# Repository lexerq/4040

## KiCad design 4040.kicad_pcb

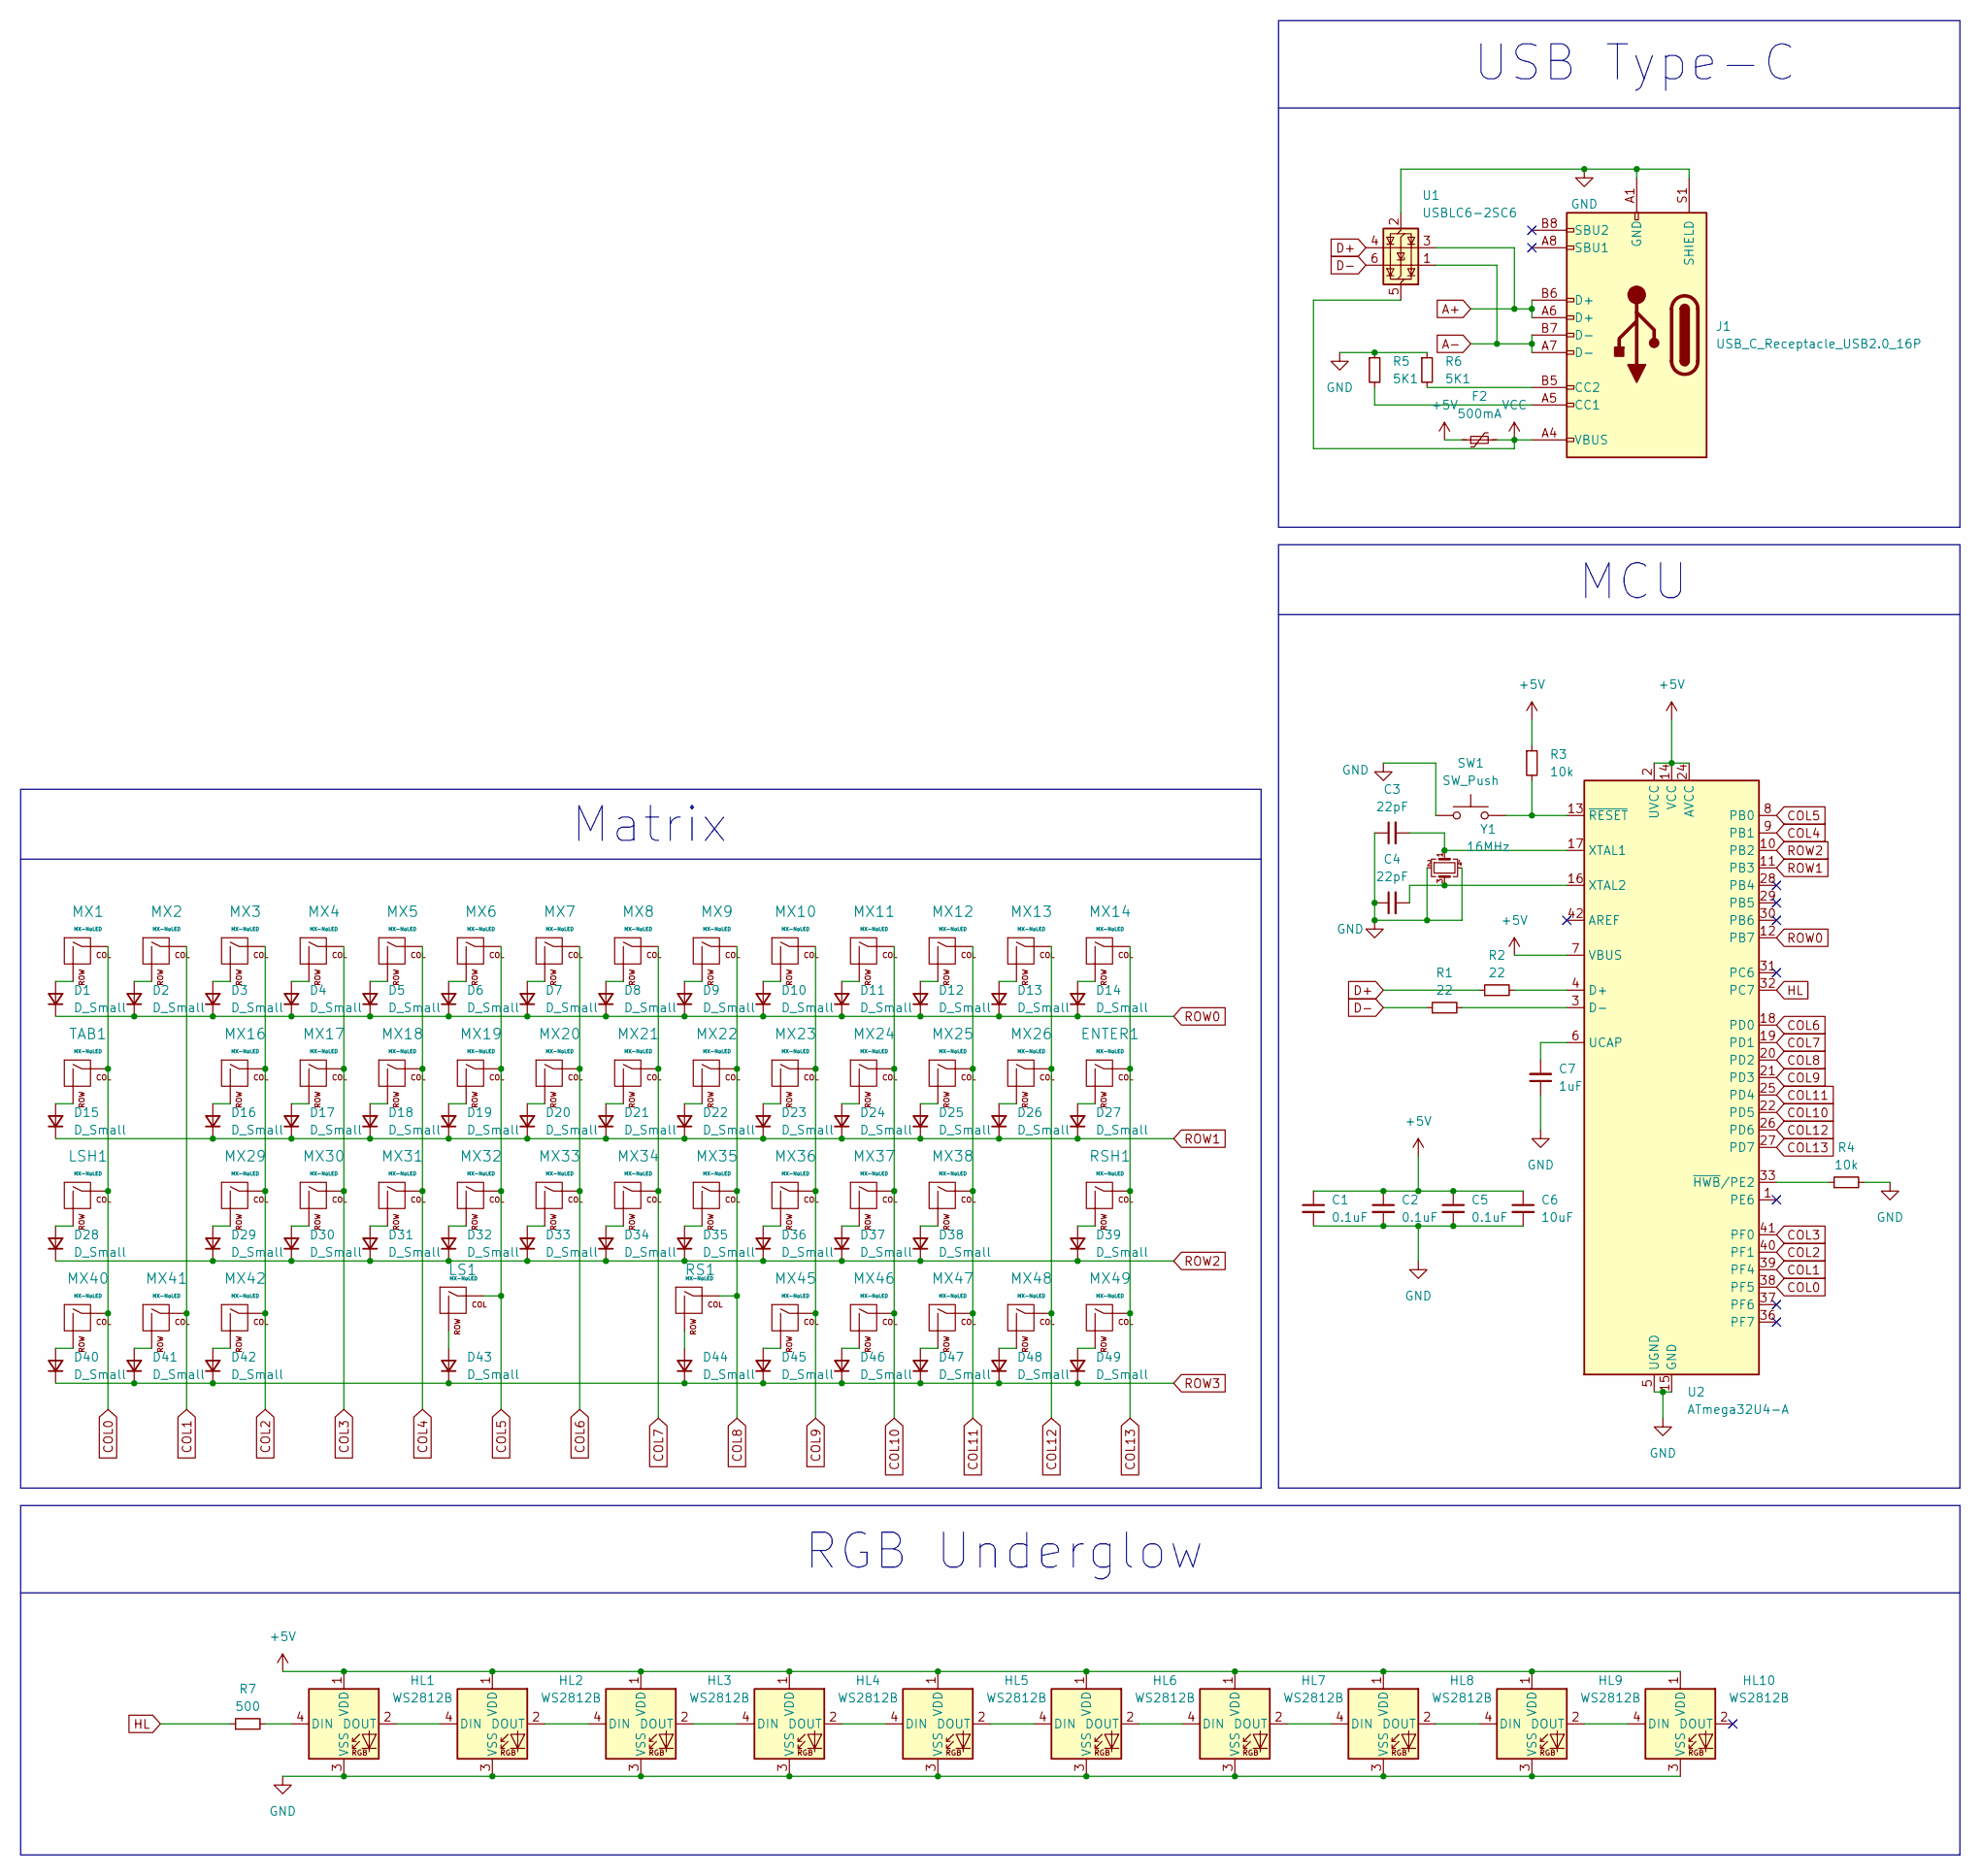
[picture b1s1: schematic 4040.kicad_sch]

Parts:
C1, C2, C5: 0.1uF; C_0805_2012Metric
C3, C4: 22pF; C_0805_2012Metric
C6: 10uF; C_0805_2012Metric
C7: 1uF; C_0805_2012Metric
D1, D2, D3, D4, D5, D6, D7, D8, D9, D10, D11, D12, D13, D14, D15, D16, D17, D18, D19, D20, D21, D22, D23, D24, D25, D26, D27, D28, D29, D30, D31, D32, D33, D34, D35, D36, D37, D38, D39, D40, D41, D42, D43, D44, D45, D46, D47, D48, D49: D_Small; 5,5ForKBD
ENTER1: MX-NoLED; MX-2.25U-NoLED
F2: 500mA; Fuse_1206_3216Metric
HL1, HL2, HL3, HL4, HL5, HL6, HL7, HL8, HL9, HL10: WS2812B; LED_WS2812B_PLCC4_5.0x5.0mm_P3.2mm
J1: USB_C_Receptacle_USB2.0_16P; USB_C_Receptacle_HRO_TYPE-C-31-M-12
LS1: MX-NoLED; MX-2.25U-ReversedStabilizers-NoLED
LSH1: MX-NoLED; MX-2U-NoLED
MX1, MX2, MX3, MX4, MX5, MX6, MX7, MX8, MX9, MX10, MX11, MX12, MX13, MX16, MX17, MX18, MX19, MX20, MX21, MX22, MX23, MX24, MX25, MX26, MX29, MX30, MX31, MX32, MX33, MX34, MX35, MX36, MX37, MX38, MX45: MX-NoLED; MX-1U-NoLED
MX14: MX-NoLED; MX-1.75U-NoLED
MX40, MX41, MX42, MX46, MX47, MX48, MX49: MX-NoLED; MX-1.25U-NoLED
R1, R2: 22; R_0805_2012Metric
R3, R4: 10k; R_0805_2012Metric
R5, R6: 5K1; R_0805_2012Metric
R7: 500; R_0805_2012Metric
RS1: MX-NoLED; MX-2.75U-ReversedStabilizers-NoLED
RSH1: MX-NoLED; MX-2.75U-NoLED
SW1: SW_Push; SW_DIP_SPSTx01_Slide_Omron_A6S-110x_W8.9mm_P2.54mm
TAB1: MX-NoLED; MX-1.5U-NoLED
U1: USBLC6-2SC6; SOT-23-6
U2: ATmega32U4-A; TQFP-44_10x10mm_P0.8mm
Y1: 16MHz; Crystal_SMD_3225-4Pin_3.2x2.5mm

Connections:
+5V: C1.1, C2.1, C5.1, C6.1, F2.1, HL1.1 (VDD), HL2.1 (VDD), HL3.1 (VDD), HL4.1 (VDD), HL5.1 (VDD), HL6.1 (VDD), HL7.1 (VDD), HL8.1 (VDD), HL9.1 (VDD), HL10.1 (VDD), R3.1, U2.2 (UVCC), U2.7 (VBUS), U2.14 (VCC), U2.24 (AVCC), U2.34 (VCC), U2.44 (AVCC)
A+: J1.A6 (D+), J1.B6 (D+), U1.3 (I/O2)
A-: J1.A7 (D-), J1.B7 (D-), U1.1 (I/O1)
COL0: LSH1.1 (COL), MX1.1 (COL), MX40.1 (COL), TAB1.1 (COL), U2.38 (PF5)
COL1: MX2.1 (COL), MX41.1 (COL), U2.39 (PF4)
COL2: MX3.1 (COL), MX16.1 (COL), MX29.1 (COL), MX42.1 (COL), U2.40 (PF1)
COL3: MX4.1 (COL), MX17.1 (COL), MX30.1 (COL), U2.41 (PF0)
COL4: MX5.1 (COL), MX18.1 (COL), MX31.1 (COL), U2.9 (PB1)
COL5: LS1.1 (COL), MX6.1 (COL), MX19.1 (COL), MX32.1 (COL), U2.8 (PB0)
COL6: MX7.1 (COL), MX20.1 (COL), MX33.1 (COL), U2.18 (PD0)
COL7: MX8.1 (COL), MX21.1 (COL), MX34.1 (COL), U2.19 (PD1)
COL8: MX9.1 (COL), MX22.1 (COL), MX35.1 (COL), RS1.1 (COL), U2.20 (PD2)
COL9: MX10.1 (COL), MX23.1 (COL), MX36.1 (COL), MX45.1 (COL), U2.21 (PD3)
COL10: MX11.1 (COL), MX24.1 (COL), MX37.1 (COL), MX46.1 (COL), U2.22 (PD5)
COL11: MX12.1 (COL), MX25.1 (COL), MX38.1 (COL), MX47.1 (COL), U2.25 (PD4)
COL12: MX13.1 (COL), MX26.1 (COL), MX48.1 (COL), U2.26 (PD6)
COL13: ENTER1.1 (COL), MX14.1 (COL), MX49.1 (COL), RSH1.1 (COL), U2.27 (PD7)
D+: R2.1, U1.4 (I/O2)
D-: R1.1, U1.6 (I/O1)
GND: C1.2, C2.2, C3.1, C4.1, C5.2, C6.2, C7.1, HL1.3 (VSS), HL2.3 (VSS), HL3.3 (VSS), HL4.3 (VSS), HL5.3 (VSS), HL6.3 (VSS), HL7.3 (VSS), HL8.3 (VSS), HL9.3 (VSS), HL10.3 (VSS), J1.A1 (GND), J1.A12 (GND), J1.B1 (GND), J1.B12 (GND), J1.S1 (SHIELD), R4.2, R5.1, R6.1, SW1.1, U1.2 (GND), U2.5 (UGND), U2.15 (GND), U2.23 (GND), U2.35 (GND), U2.43 (GND), Y1.2, Y1.4
HL: R7.1, U2.32 (PC7)
unnamed: D1.2 (A), MX1.2 (ROW)
unnamed: D2.2 (A), MX2.2 (ROW)
unnamed: D3.2 (A), MX3.2 (ROW)
unnamed: D4.2 (A), MX4.2 (ROW)
unnamed: D5.2 (A), MX5.2 (ROW)
unnamed: D6.2 (A), MX6.2 (ROW)
unnamed: D7.2 (A), MX7.2 (ROW)
unnamed: D8.2 (A), MX8.2 (ROW)
unnamed: D9.2 (A), MX9.2 (ROW)
unnamed: D10.2 (A), MX10.2 (ROW)
unnamed: D11.2 (A), MX11.2 (ROW)
unnamed: D12.2 (A), MX12.2 (ROW)
unnamed: D13.2 (A), MX13.2 (ROW)
unnamed: D14.2 (A), MX14.2 (ROW)
unnamed: D15.2 (A), TAB1.2 (ROW)
unnamed: D16.2 (A), MX16.2 (ROW)
unnamed: D17.2 (A), MX17.2 (ROW)
unnamed: D18.2 (A), MX18.2 (ROW)
unnamed: D19.2 (A), MX19.2 (ROW)
unnamed: D20.2 (A), MX20.2 (ROW)
unnamed: D21.2 (A), MX21.2 (ROW)
unnamed: D22.2 (A), MX22.2 (ROW)
unnamed: D23.2 (A), MX23.2 (ROW)
unnamed: D24.2 (A), MX24.2 (ROW)
unnamed: D25.2 (A), MX25.2 (ROW)
unnamed: D26.2 (A), MX26.2 (ROW)
unnamed: D27.2 (A), ENTER1.2 (ROW)
unnamed: D28.2 (A), LSH1.2 (ROW)
unnamed: D29.2 (A), MX29.2 (ROW)
unnamed: D30.2 (A), MX30.2 (ROW)
unnamed: D31.2 (A), MX31.2 (ROW)
unnamed: D32.2 (A), MX32.2 (ROW)
unnamed: D33.2 (A), MX33.2 (ROW)
unnamed: D34.2 (A), MX34.2 (ROW)
unnamed: D35.2 (A), MX35.2 (ROW)
unnamed: D36.2 (A), MX36.2 (ROW)
unnamed: D37.2 (A), MX37.2 (ROW)
unnamed: D38.2 (A), MX38.2 (ROW)
unnamed: D39.2 (A), RSH1.2 (ROW)
unnamed: D40.2 (A), MX40.2 (ROW)
unnamed: D41.2 (A), MX41.2 (ROW)
unnamed: D42.2 (A), MX42.2 (ROW)
unnamed: D43.2 (A), LS1.2 (ROW)
unnamed: D44.2 (A), RS1.2 (ROW)
unnamed: D45.2 (A), MX45.2 (ROW)
unnamed: D46.2 (A), MX46.2 (ROW)
unnamed: D47.2 (A), MX47.2 (ROW)
unnamed: D48.2 (A), MX48.2 (ROW)
unnamed: D49.2 (A), MX49.2 (ROW)
unnamed: HL1.4 (DIN), R7.2
unnamed: HL1.2 (DOUT), HL2.4 (DIN)
unnamed: HL2.2 (DOUT), HL3.4 (DIN)
unnamed: HL3.2 (DOUT), HL4.4 (DIN)
unnamed: HL4.2 (DOUT), HL5.4 (DIN)
unnamed: HL5.2 (DOUT), HL6.4 (DIN)
unnamed: HL6.2 (DOUT), HL7.4 (DIN)
unnamed: HL7.2 (DOUT), HL8.4 (DIN)
unnamed: HL8.2 (DOUT), HL9.4 (DIN)
unnamed: HL9.2 (DOUT), HL10.4 (DIN)
unnamed: J1.A5 (CC1), R5.2
unnamed: J1.B5 (CC2), R6.2
unnamed: R2.2, U2.4 (D+)
unnamed: R1.2, U2.3 (D-)
unnamed: C7.2, U2.6 (UCAP)
unnamed: C3.2, U2.17 (XTAL1), Y1.1
unnamed: C4.2, U2.16 (XTAL2), Y1.3
unnamed: R4.1, U2.33 (~HWB/PE2)
unnamed: R3.2, SW1.2, U2.13 (~RESET)
ROW0: D1.1 (K), D2.1 (K), D3.1 (K), D4.1 (K), D5.1 (K), D6.1 (K), D7.1 (K), D8.1 (K), D9.1 (K), D10.1 (K), D11.1 (K), D12.1 (K), D13.1 (K), D14.1 (K), U2.12 (PB7)
ROW1: D15.1 (K), D16.1 (K), D17.1 (K), D18.1 (K), D19.1 (K), D20.1 (K), D21.1 (K), D22.1 (K), D23.1 (K), D24.1 (K), D25.1 (K), D26.1 (K), D27.1 (K), U2.11 (PB3)
ROW2: D28.1 (K), D29.1 (K), D30.1 (K), D31.1 (K), D32.1 (K), D33.1 (K), D34.1 (K), D35.1 (K), D36.1 (K), D37.1 (K), D38.1 (K), D39.1 (K), U2.10 (PB2)
ROW3: D40.1 (K), D41.1 (K), D42.1 (K), D43.1 (K), D44.1 (K), D45.1 (K), D46.1 (K), D47.1 (K), D48.1 (K), D49.1 (K)
VCC: F2.2, J1.A4 (VBUS), J1.A9 (VBUS), J1.B4 (VBUS), J1.B9 (VBUS), U1.5 (VBUS)

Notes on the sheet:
MCU
RGB Underglow
Matrix
USB Type-C

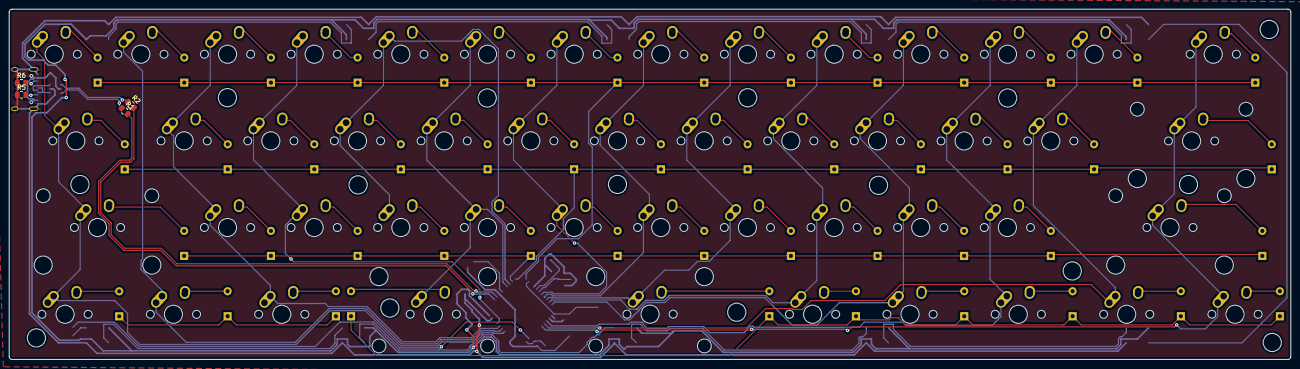
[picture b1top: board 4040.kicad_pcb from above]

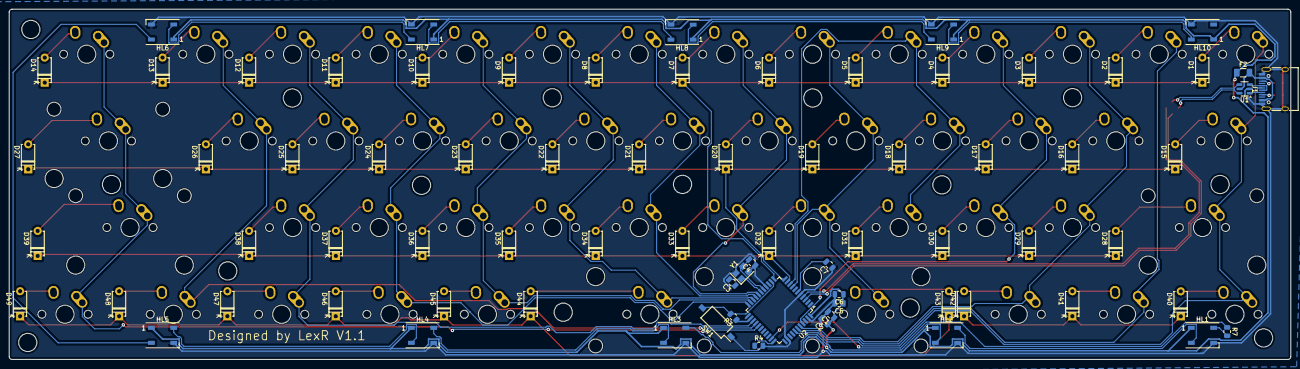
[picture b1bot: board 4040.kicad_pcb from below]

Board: 2 copper layers, 281.7 x 77.0 mm, 128 parts (75 on the bottom side), 94 nets.

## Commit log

2024-08-21 main
2024-12-22 pictures
2024-12-22 README.md
